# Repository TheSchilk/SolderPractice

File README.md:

# SMD Solder Practice

### Philipp Schilk

A 100x100mm board with various SMD component footprints to practice SMD soldering.

## Components:

| Footprint 	| Count 	| KiCad Footprint 	|
|-	|-	|-	|
| MELF D 	| 12 	| Diode_SMD:D_MELF 	|
| 0805 R 	| 12 	| Resistor_SMD:R_0805_2012Metric 	|
| 0805 D 	| 12 	| LED_SMD:LED_0805_2012Metric 	|
| 0603 R 	| 12 	| Resistor_SMD:R_0603_1608Metric 	|
| 0603 D 	| 12 	| LED_SMD:LED_0603_1608Metric 	|
| 0402 R 	| 12 	| Resistor_SMD:R_0402_1005Metric 	|
| 0402 D 	| 12 	| LED_SMD:LED_0402_1005Metric 	|
| 0201 R 	| 12 	| Resistor_SMD:R_0201_0603Metric 	|
| 0201 D 	| 12 	| LED_SMD:LED_0201_0603Metric 	|
| 01005 R 	| 12 	| Resistor_SMD:R_01005_0402Metric 	|
| 01005 D 	| 12 	| LED_SMD:LED_01005_0402Metric 	|
| SOD-523 D 	| 12 	| Diode_SMD:D_SOD-523 	|
| SOT-23 	| 16 	| Package_TO_SOT_SMD:SOT-23 	|
| TO-252-2/DPAK 	| 4 	| Package_TO_SOT_SMD:TO-252-3_TabPin2 	|
| SOT-223 	| 4 	| Package_TO_SOT_SMD:SOT-223-3_TabPin2 	|
| SSOP-24 	| 8 	| Package_SO:SSOP-24_5.3x8.2mm_P0.65mm 	|
| QFN-20 	| 8 	| Package_DFN_QFN:QFN-20-1EP_4x4mm_P0.5mm_EP2.5x2.5mm 	|
| SOIC-8 	| 8 	| Package_SO:SOIC-8_3.9x4.9mm_P1.27mm 	|
| SOIC-16 	| 8 	| Package_SO:SOIC-16_3.9x9.9mm_P1.27mm 	|
| LQFP-32 	| 4 	| Package_QFP:LQFP-32_7x7mm_P0.8mm 	|
| LQFP-64 	| 4 	| Package_QFP:LQFP-64_10x10mm_P0.5mm 	|
| 10pin TH Header 	| 5 	| Connector_PinHeader_2.54mm:PinHeader_1x10_P2.54mm_Vertical

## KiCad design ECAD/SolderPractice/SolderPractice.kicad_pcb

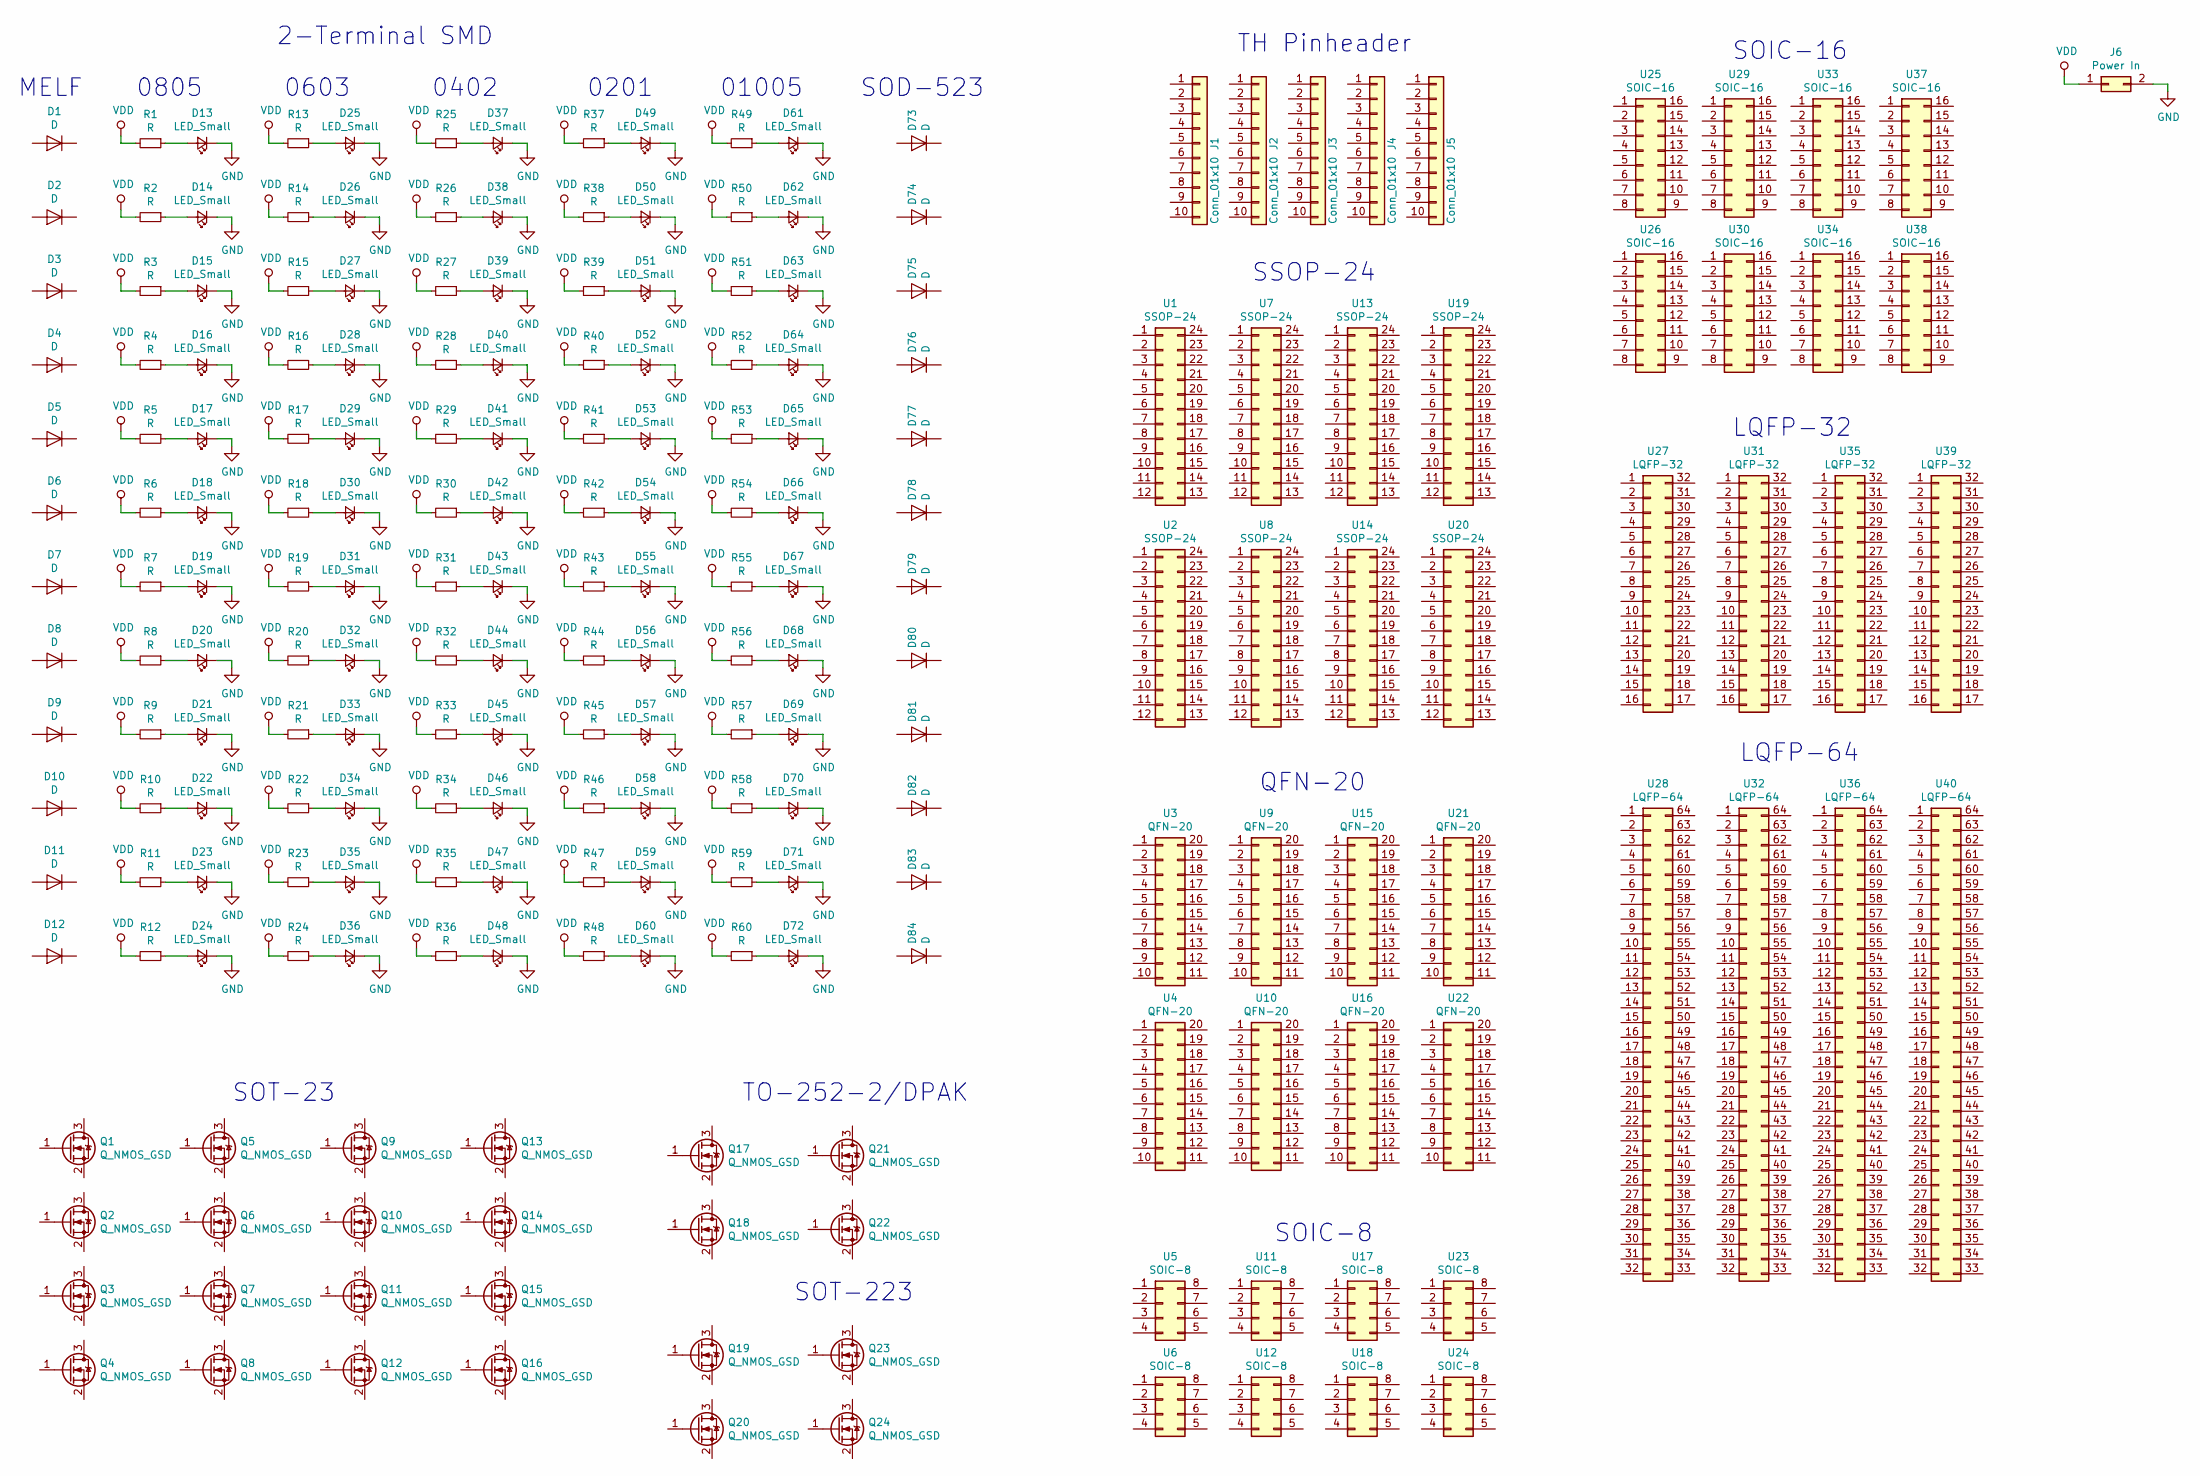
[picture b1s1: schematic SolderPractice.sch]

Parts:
D1, D2, D3, D4, D5, D6, D7, D8, D9, D10, D11, D12: D; D_MELF
D13, D14, D15, D16, D17, D18, D19, D20, D21, D22, D23, D24: LED_Small; LED_0805_2012Metric
D25, D26, D27, D28, D29, D30, D31, D32, D33, D34, D35, D36: LED_Small; LED_0603_1608Metric
D37, D38, D39, D40, D41, D42, D43, D44, D45, D46, D47, D48: LED_Small; LED_0402_1005Metric
D49, D50, D51, D52, D53, D54, D55, D56, D57, D58, D59, D60: LED_Small; LED_0201_0603Metric
D61, D62, D63, D64, D65, D66, D67, D68, D69, D70, D71, D72: LED_Small; LED_01005_0402Metric
D73, D74, D75, D76, D77, D78, D79, D80, D81, D82, D83, D84: D; D_SOD-523
J1, J2, J3, J4, J5: Conn_01x10; PinHeader_1x10_P2.54mm_Vertical
J6: Power In; PinHeader_1x02_P2.54mm_Vertical
Q1, Q2, Q3, Q4, Q5, Q6, Q7, Q8, Q9, Q10, Q11, Q12, Q13, Q14, Q15, Q16: Q_NMOS_GSD; SOT-23
Q17, Q18, Q21, Q22: Q_NMOS_GSD; TO-252-3_TabPin2
Q19, Q20, Q23, Q24: Q_NMOS_GSD; SOT-223-3_TabPin2
R1, R2, R3, R4, R5, R6, R7, R8, R9, R10, R11, R12: R; R_0805_2012Metric
R13, R14, R15, R16, R17, R18, R19, R20, R21, R22, R23, R24: R; R_0603_1608Metric
R25, R26, R27, R28, R29, R30, R31, R32, R33, R34, R35, R36: R; R_0402_1005Metric
R37, R38, R39, R40, R41, R42, R43, R44, R45, R46, R47, R48: R; R_0201_0603Metric
R49, R50, R51, R52, R53, R54, R55, R56, R57, R58, R59, R60: R; R_01005_0402Metric
U1, U2, U7, U8, U13, U14, U19, U20: SSOP-24; SSOP-24_5.3x8.2mm_P0.65mm
U3, U4, U9, U10, U15, U16, U21, U22: QFN-20; QFN-20-1EP_4x4mm_P0.5mm_EP2.5x2.5mm
U5, U6, U11, U12, U17, U18, U23, U24: SOIC-8; SOIC-8_3.9x4.9mm_P1.27mm
U25, U26, U29, U30, U33, U34, U37, U38: SOIC-16; SOIC-16_3.9x9.9mm_P1.27mm
U27, U31, U35, U39: LQFP-32; LQFP-32_7x7mm_P0.8mm
U28, U32, U36, U40: LQFP-64; LQFP-64_10x10mm_P0.5mm

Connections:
GND: D13.1 (K), D14.1 (K), D15.1 (K), D16.1 (K), D17.1 (K), D18.1 (K), D19.1 (K), D20.1 (K), D21.1 (K), D22.1 (K), D23.1 (K), D24.1 (K), D25.1 (K), D26.1 (K), D27.1 (K), D28.1 (K), D29.1 (K), D30.1 (K), D31.1 (K), D32.1 (K), D33.1 (K), D34.1 (K), D35.1 (K), D36.1 (K), D37.1 (K), D38.1 (K), D39.1 (K), D40.1 (K), D41.1 (K), D42.1 (K), D43.1 (K), D44.1 (K), D45.1 (K), D46.1 (K), D47.1 (K), D48.1 (K), D49.1 (K), D50.1 (K), D51.1 (K), D52.1 (K), D53.1 (K), D54.1 (K), D55.1 (K), D56.1 (K), D57.1 (K), D58.1 (K), D59.1 (K), D60.1 (K), D61.1 (K), D62.1 (K), D63.1 (K), D64.1 (K), D65.1 (K), D66.1 (K), D67.1 (K), D68.1 (K), D69.1 (K), D70.1 (K), D71.1 (K), D72.1 (K), J6.2
unnamed: D13.2 (A), R1.1
unnamed: D14.2 (A), R2.1
unnamed: D15.2 (A), R3.1
unnamed: D16.2 (A), R4.1
unnamed: D17.2 (A), R5.1
unnamed: D18.2 (A), R6.1
unnamed: D19.2 (A), R7.1
unnamed: D20.2 (A), R8.1
unnamed: D21.2 (A), R9.1
unnamed: D22.2 (A), R10.1
unnamed: D23.2 (A), R11.1
unnamed: D24.2 (A), R12.1
unnamed: D25.2 (A), R13.1
unnamed: D26.2 (A), R14.1
unnamed: D27.2 (A), R15.1
unnamed: D28.2 (A), R16.1
unnamed: D29.2 (A), R17.1
unnamed: D30.2 (A), R18.1
unnamed: D31.2 (A), R19.1
unnamed: D32.2 (A), R20.1
unnamed: D33.2 (A), R21.1
unnamed: D34.2 (A), R22.1
unnamed: D35.2 (A), R23.1
unnamed: D36.2 (A), R24.1
unnamed: D37.2 (A), R25.1
unnamed: D38.2 (A), R26.1
unnamed: D39.2 (A), R27.1
unnamed: D40.2 (A), R28.1
unnamed: D41.2 (A), R29.1
unnamed: D42.2 (A), R30.1
unnamed: D43.2 (A), R31.1
unnamed: D44.2 (A), R32.1
unnamed: D45.2 (A), R33.1
unnamed: D46.2 (A), R34.1
unnamed: D47.2 (A), R35.1
unnamed: D48.2 (A), R36.1
unnamed: D49.2 (A), R37.1
unnamed: D50.2 (A), R38.1
unnamed: D51.2 (A), R39.1
unnamed: D52.2 (A), R40.1
unnamed: D53.2 (A), R41.1
unnamed: D54.2 (A), R42.1
unnamed: D55.2 (A), R43.1
unnamed: D56.2 (A), R44.1
unnamed: D57.2 (A), R45.1
unnamed: D58.2 (A), R46.1
unnamed: D59.2 (A), R47.1
unnamed: D60.2 (A), R48.1
unnamed: D61.2 (A), R49.1
unnamed: D62.2 (A), R50.1
unnamed: D63.2 (A), R51.1
unnamed: D64.2 (A), R52.1
unnamed: D65.2 (A), R53.1
unnamed: D66.2 (A), R54.1
unnamed: D67.2 (A), R55.1
unnamed: D68.2 (A), R56.1
unnamed: D69.2 (A), R57.1
unnamed: D70.2 (A), R58.1
unnamed: D71.2 (A), R59.1
unnamed: D72.2 (A), R60.1
VDD: J6.1, R1.2, R2.2, R3.2, R4.2, R5.2, R6.2, R7.2, R8.2, R9.2, R10.2, R11.2, R12.2, R13.2, R14.2, R15.2, R16.2, R17.2, R18.2, R19.2, R20.2, R21.2, R22.2, R23.2, R24.2, R25.2, R26.2, R27.2, R28.2, R29.2, R30.2, R31.2, R32.2, R33.2, R34.2, R35.2, R36.2, R37.2, R38.2, R39.2, R40.2, R41.2, R42.2, R43.2, R44.2, R45.2, R46.2, R47.2, R48.2, R49.2, R50.2, R51.2, R52.2, R53.2, R54.2, R55.2, R56.2, R57.2, R58.2, R59.2, R60.2

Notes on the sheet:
2-Terminal SMD
TH Pinheader
SSOP-24
QFN-20
SOT-23
LQFP-32
SOIC-8
SOD-523
0805
01005
0201
0402
0603
MELF
SOIC-16
LQFP-64
TO-252-2/DPAK
SOT-223

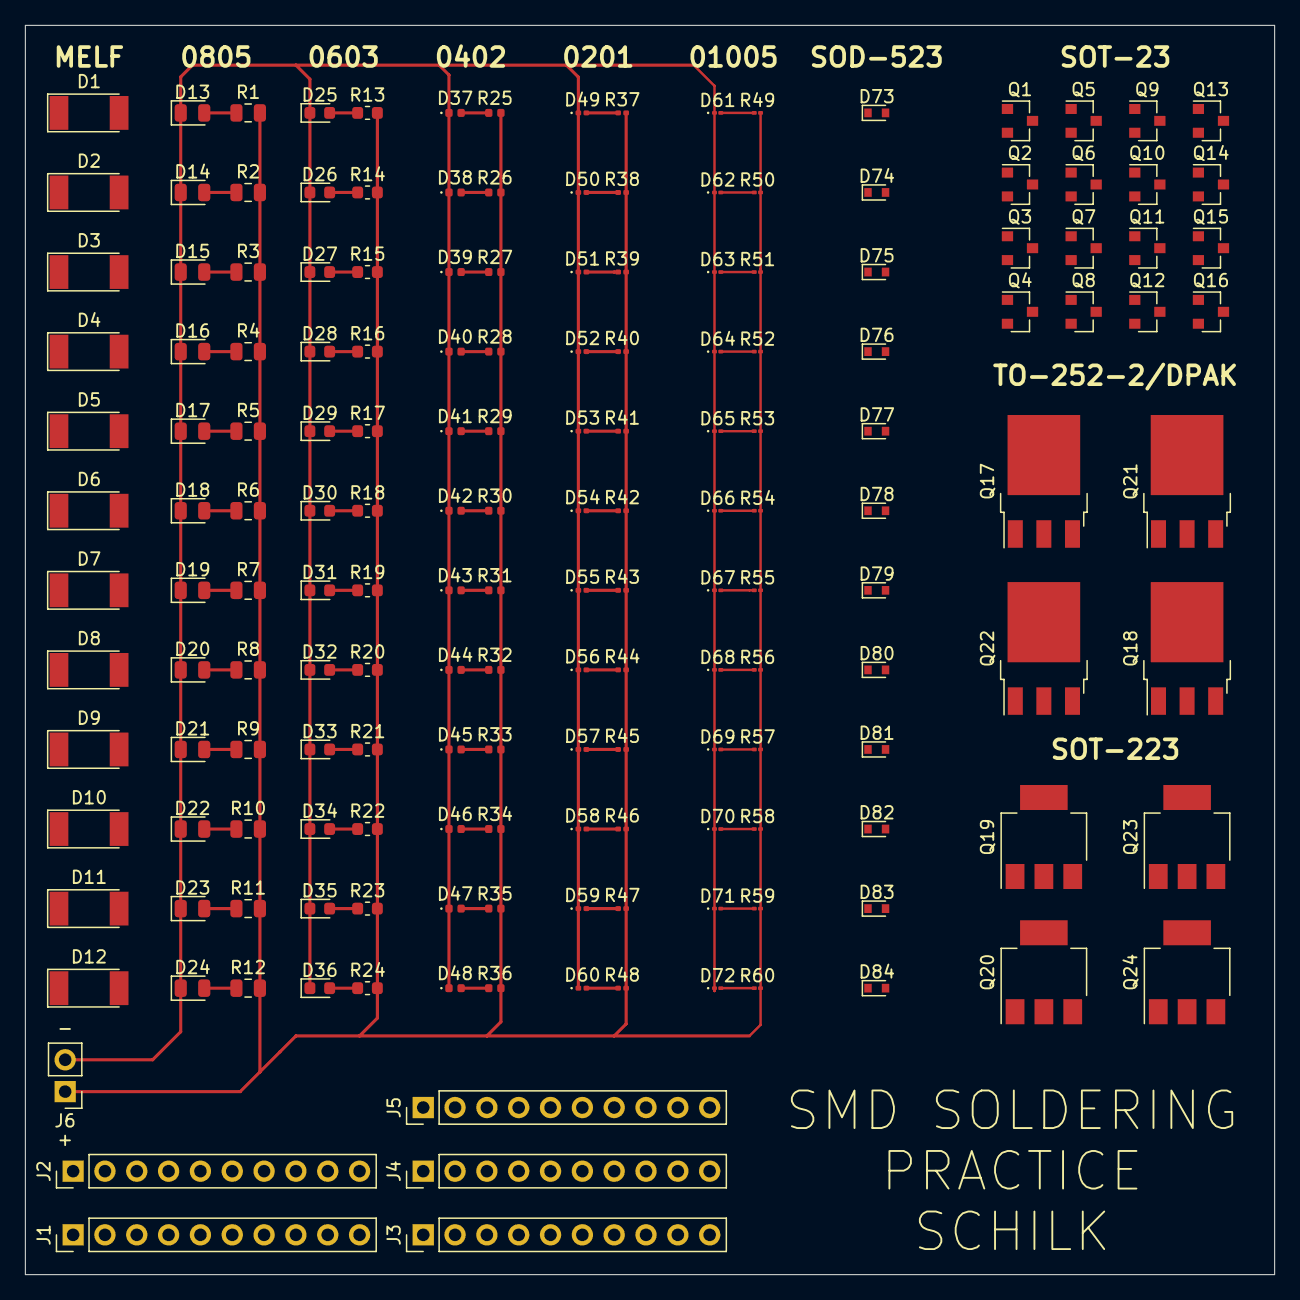
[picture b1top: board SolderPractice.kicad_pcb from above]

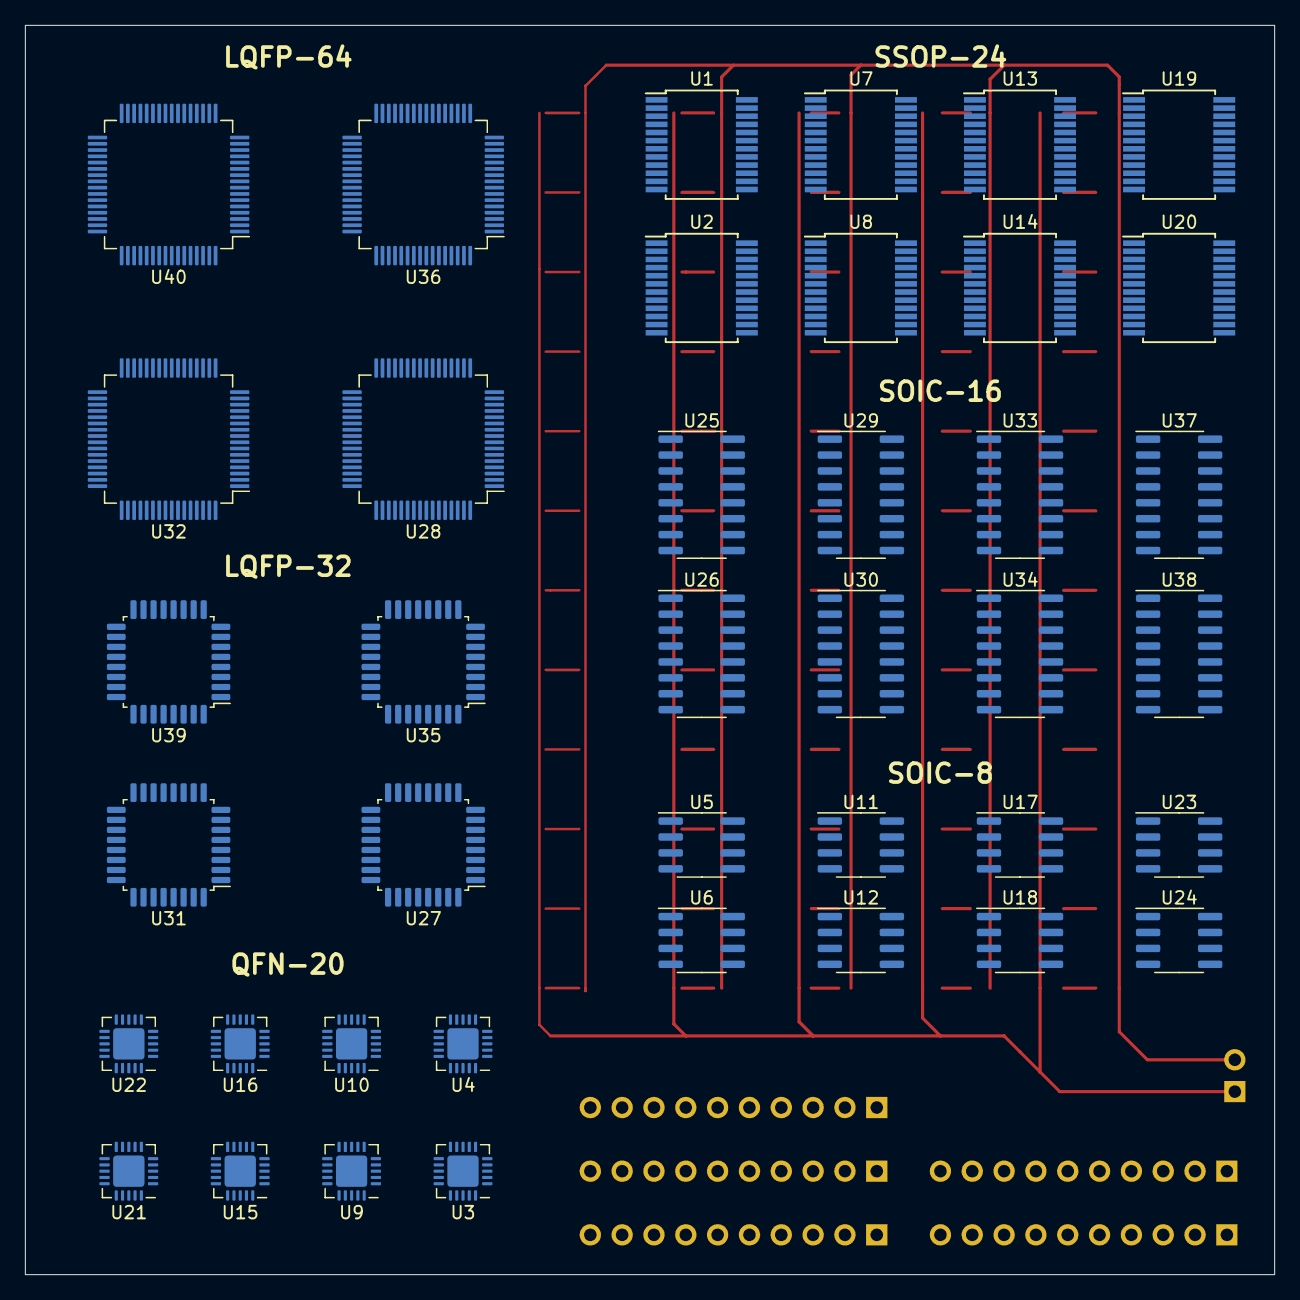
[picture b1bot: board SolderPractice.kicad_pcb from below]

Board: 2 copper layers, 99.7 x 99.7 mm, 214 parts (40 on the bottom side), 62 nets.

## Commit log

2021-05-24 Show KiCad in github language stats
